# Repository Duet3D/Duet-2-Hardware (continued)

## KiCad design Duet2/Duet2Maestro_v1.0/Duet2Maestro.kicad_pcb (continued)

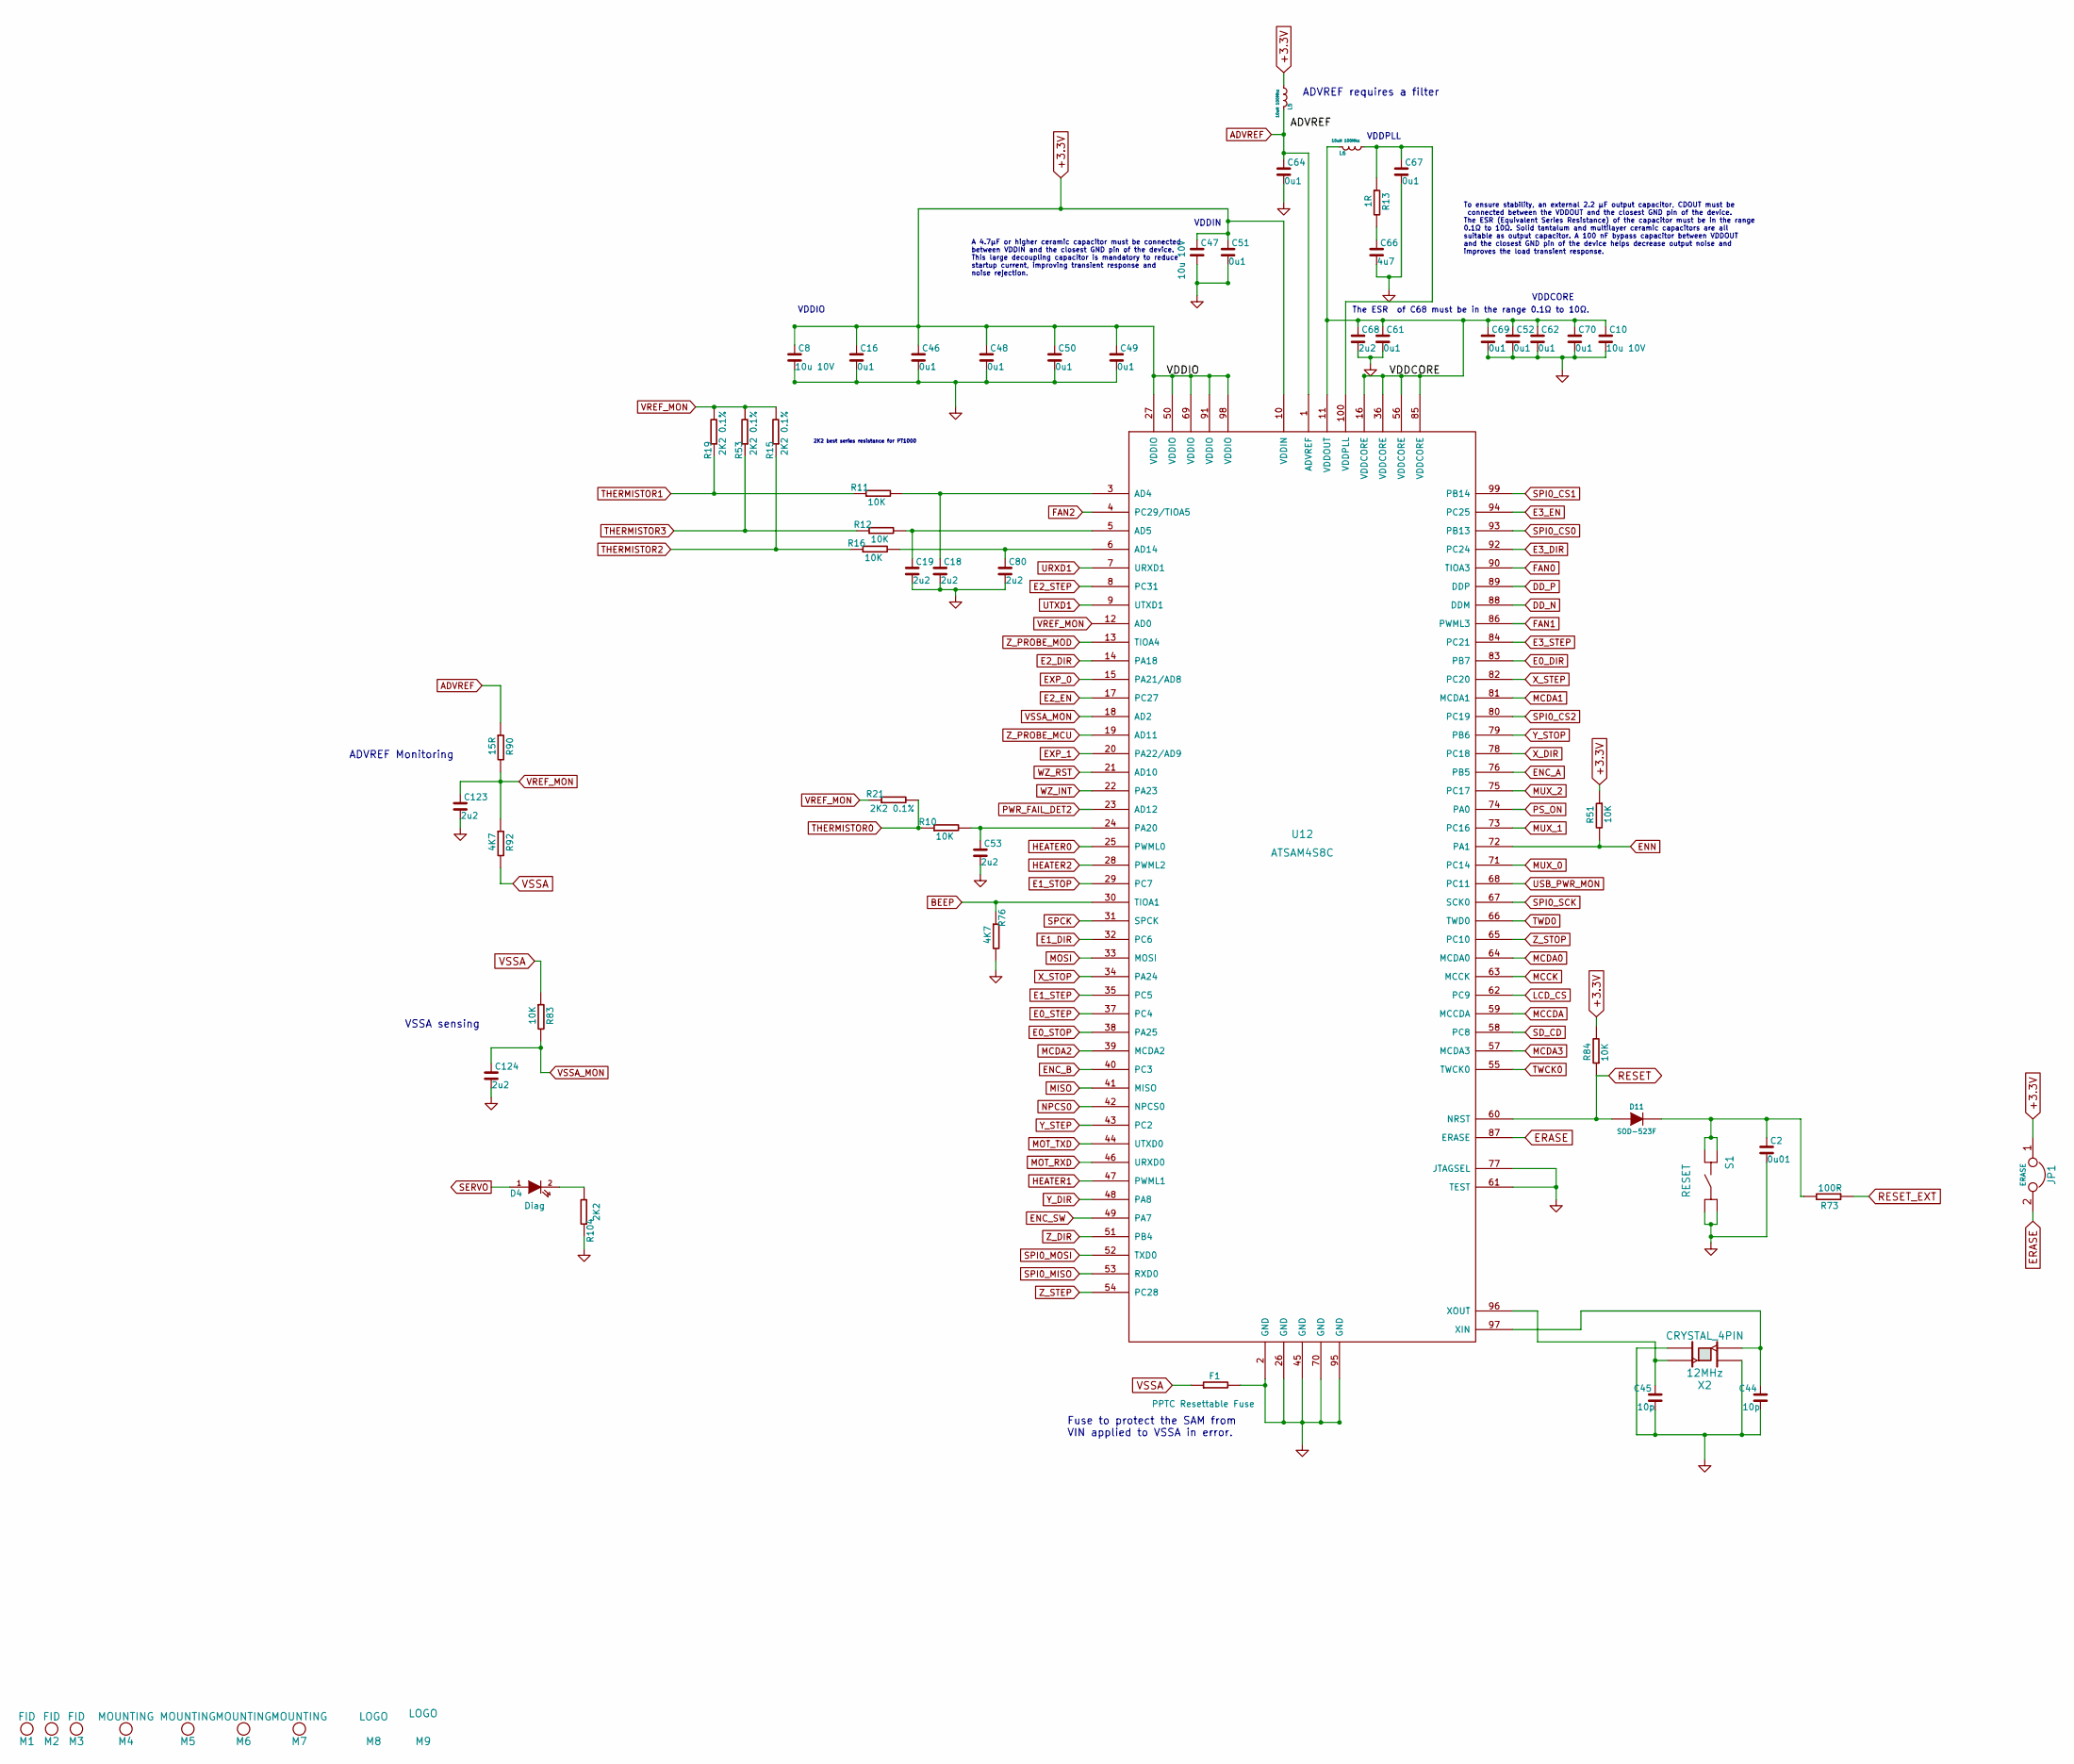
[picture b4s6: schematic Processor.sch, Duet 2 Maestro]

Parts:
C2: 0u01; C_0603
C8, C10, C47: 10u 10V; C_0805
C16, C46, C48, C49, C50, C51, C52, C61, C62, C64, C67, C69, C70: 0u1; C_0603
C18, C19, C53, C68, C80, C123, C124: 2u2; C_0603
C44, C45: 10p; C_0603
C66: 4u7; C_0805
D4: Diag; D_0603
D11: SOD-523F
F1: PPTC Resettable Fuse; R_1206
JP1: ERASE; JUMPER
L5, L6: 10uH 100Mhz; R_0603
M1, M2, M3: FID; Fiducial_1mm_Dia_2.54mm_Outer_CopperTop
M4, M5, M6, M7: MOUNTING; Fixing_M4
M8: LOGO; LOGO1
M9: LOGO; Plain_Wifi_Logo_m
R10, R11, R12, R16, R51, R83, R84: 10K; R_0603
R13: 1R; R_0603
R15, R19, R21, R53: 2K2 0.1%; R_0603
R73: 100R; R_0603
R76, R92: 4K7; R_0603
R90: 15R; R_0603
R104: 2K2; R_0603
S1: RESET; SW_SIDE_1_lugs
U12: ATSAM4S8C; LQFP-100_14x14mm_Pitch0.5mm
X2: CRYSTAL_4PIN; Xtal_5x3.2

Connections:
+3.3V: C8.1, C16.1, C46.1, C47.1, C48.1, C49.1, C50.1, C51.1, JP1.1, L5.2 (B), R51.1, R84.2, U12.10 (VDDIN), U12.27 (VDDIO), U12.50 (VDDIO), U12.69 (VDDIO), U12.91 (VDDIO), U12.98 (VDDIO); also elsewhere on the board
/Processor/VDDCORE: C10.1, C52.1, C61.1, C62.1, C68.1, C69.1, C70.1, L6.1 (A), U12.11 (VDDOUT), U12.16 (VDDCORE), U12.36 (VDDCORE), U12.56 (VDDCORE), U12.85 (VDDCORE)
ADVREF: C64.1, L5.1 (A), R90.1, U12.1 (ADVREF); also elsewhere on the board
BEEP: R76.1, U12.30 (TIOA1); also elsewhere on the board
DD_N: U12.88 (DDM); also elsewhere on the board
DD_P: U12.89 (DDP); also elsewhere on the board
E0_DIR: U12.83 (PB7); also elsewhere on the board
E0_STEP: U12.37 (PC4); also elsewhere on the board
E0_STOP: U12.38 (PA25); also elsewhere on the board
E1_DIR: U12.32 (PC6); also elsewhere on the board
E1_STEP: U12.35 (PC5); also elsewhere on the board
E1_STOP: U12.29 (PC7); also elsewhere on the board
E2_DIR: U12.14 (PA18); also elsewhere on the board
E2_EN: U12.17 (PC27); also elsewhere on the board
E2_STEP: U12.8 (PC31); also elsewhere on the board
E3_DIR: U12.92 (PC24); also elsewhere on the board
E3_EN: U12.94 (PC25); also elsewhere on the board
E3_STEP: U12.84 (PC21); also elsewhere on the board
ENC_A: U12.76 (PB5); also elsewhere on the board
ENC_B: U12.40 (PC3); also elsewhere on the board
ENC_SW: U12.49 (PA7); also elsewhere on the board
ENN: R51.2, U12.72 (PA1); also elsewhere on the board
ERASE: JP1.2, U12.87 (ERASE)
EXP_0: U12.15 (PA21/AD8); also elsewhere on the board
EXP_1: U12.20 (PA22/AD9); also elsewhere on the board
FAN0: U12.90 (TIOA3); also elsewhere on the board
FAN1: U12.86 (PWML3); also elsewhere on the board
FAN2: U12.4 (PC29/TIOA5); also elsewhere on the board
GND: C2.2, C8.2, C10.2, C16.2, C18.2, C19.2, C44.2, C45.2, C46.2, C47.2, C48.2, C49.2, C50.2, C51.2, C52.2, C53.2, C61.2, C62.2, C64.2, C66.2, C67.2, C68.2, C69.2, C70.2, C80.2, C123.2, C124.2, F1.2, R76.2, R104.1, S1.1, S1.2, U12.2 (GND), U12.26 (GND), U12.45 (GND), U12.61 (TEST), U12.70 (GND), U12.77 (JTAGSEL), U12.95 (GND), X2.2, X2.4; also elsewhere on the board
HEATER0: U12.25 (PWML0); also elsewhere on the board
HEATER1: U12.47 (PWML1); also elsewhere on the board
HEATER2: U12.28 (PWML2); also elsewhere on the board
LCD_CS: U12.62 (PC9); also elsewhere on the board
MCCDA: U12.59 (MCCDA); also elsewhere on the board
MCCK: U12.63 (MCCK); also elsewhere on the board
MCDA0: U12.64 (MCDA0); also elsewhere on the board
MCDA1: U12.81 (MCDA1); also elsewhere on the board
MCDA2: U12.39 (MCDA2); also elsewhere on the board
MCDA3: U12.57 (MCDA3); also elsewhere on the board
MISO: U12.41 (MISO); also elsewhere on the board
MOSI: U12.33 (MOSI); also elsewhere on the board
MOT_RXD: U12.46 (URXD0); also elsewhere on the board
MOT_TXD: U12.44 (UTXD0); also elsewhere on the board
MUX_0: U12.71 (PC14); also elsewhere on the board
MUX_1: U12.73 (PC16); also elsewhere on the board
MUX_2: U12.75 (PC17); also elsewhere on the board
NPCS0: U12.42 (NPCS0); also elsewhere on the board
unnamed: C2.1, D11.1 (K), R73.2, S1.3, S1.4
unnamed: C18.1, R11.2, U12.3 (AD4)
unnamed: C19.1, R12.2, U12.5 (AD5)
unnamed: C44.1, U12.97 (XIN), X2.3
unnamed: C45.1, U12.96 (XOUT), X2.1
unnamed: C53.1, R10.2, U12.24 (PA20)
unnamed: C66.1, R13.2
unnamed: C67.1, L6.2 (B), R13.1, U12.100 (VDDPLL)
unnamed: C80.1, R16.2, U12.6 (AD14)
unnamed: D4.2 (K), R104.2
PS_ON: U12.74 (PA0); also elsewhere on the board
PWR_FAIL_DET2: U12.23 (AD12); also elsewhere on the board
RESET: D11.2 (A), R84.1, U12.60 (NRST); also elsewhere on the board
RESET_EXT: R73.1; also elsewhere on the board
SD_CD: U12.58 (PC8); also elsewhere on the board
SERVO: D4.1 (A); also elsewhere on the board
SPCK: U12.31 (SPCK); also elsewhere on the board
SPI0_CS0: U12.93 (PB13); also elsewhere on the board
SPI0_CS1: U12.99 (PB14); also elsewhere on the board
SPI0_CS2: U12.80 (PC19); also elsewhere on the board
SPI0_MISO: U12.53 (RXD0); also elsewhere on the board
SPI0_MOSI: U12.52 (TXD0); also elsewhere on the board
SPI0_SCK: U12.67 (SCK0); also elsewhere on the board
THERMISTOR0: R10.1, R21.2; also elsewhere on the board
THERMISTOR1: R11.1, R19.1; also elsewhere on the board
THERMISTOR2: R15.1, R16.1; also elsewhere on the board
THERMISTOR3: R12.1, R53.1; also elsewhere on the board
TWCK0: U12.55 (TWCK0); also elsewhere on the board
TWD0: U12.66 (TWD0); also elsewhere on the board
URXD1: U12.7 (URXD1); also elsewhere on the board
USB_PWR_MON: U12.68 (PC11); also elsewhere on the board
UTXD1: U12.9 (UTXD1); also elsewhere on the board
VREF_MON: C123.1, R15.2, R19.2, R21.1, R53.2, R90.2, R92.1, U12.12 (AD0)
VSSA: F1.1, R83.1, R92.2; also elsewhere on the board
VSSA_MON: C124.1, R83.2, U12.18 (AD2)
WZ_INT: U12.22 (PA23); also elsewhere on the board
WZ_RST: U12.21 (AD10); also elsewhere on the board
X_DIR: U12.78 (PC18); also elsewhere on the board
X_STEP: U12.82 (PC20); also elsewhere on the board
X_STOP: U12.34 (PA24); also elsewhere on the board
Y_DIR: U12.48 (PA8); also elsewhere on the board
Y_STEP: U12.43 (PC2); also elsewhere on the board
Y_STOP: U12.79 (PB6); also elsewhere on the board
Z_DIR: U12.51 (PB4); also elsewhere on the board
Z_PROBE_MCU: U12.19 (AD11); also elsewhere on the board
Z_PROBE_MOD: U12.13 (TIOA4); also elsewhere on the board
Z_STEP: U12.54 (PC28); also elsewhere on the board
Z_STOP: U12.65 (PC10); also elsewhere on the board

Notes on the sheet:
VDDPLL
VDDCORE
VDDIO
VDDIN
To ensure stability, an external 2.2 μF output capacitor, CDOUT must be connected between the VDDOUT and the closest GND pin of the device. The ESR (Equivalent Series Resistance) of the capacitor must be in the range 0.1Ω to 10Ω. Solid tantalum and multilayer ceramic capacitors are all suitable as 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
Fuse to protect the SAM from VIN applied to VSSA in error.
The ESR of C68 must be in the range 0.1Ω to 10Ω.
ADVREF requires a filter
VSSA sensing
A 4.7µF or higher ceramic capacitor must be connected between VDDIN and the closest GND pin of the device. This large decoupling capacitor is mandatory to reduce startup current, improving transient response and noise rejection.
2K2 best series resistance for PT1000
ADVREF Monitoring

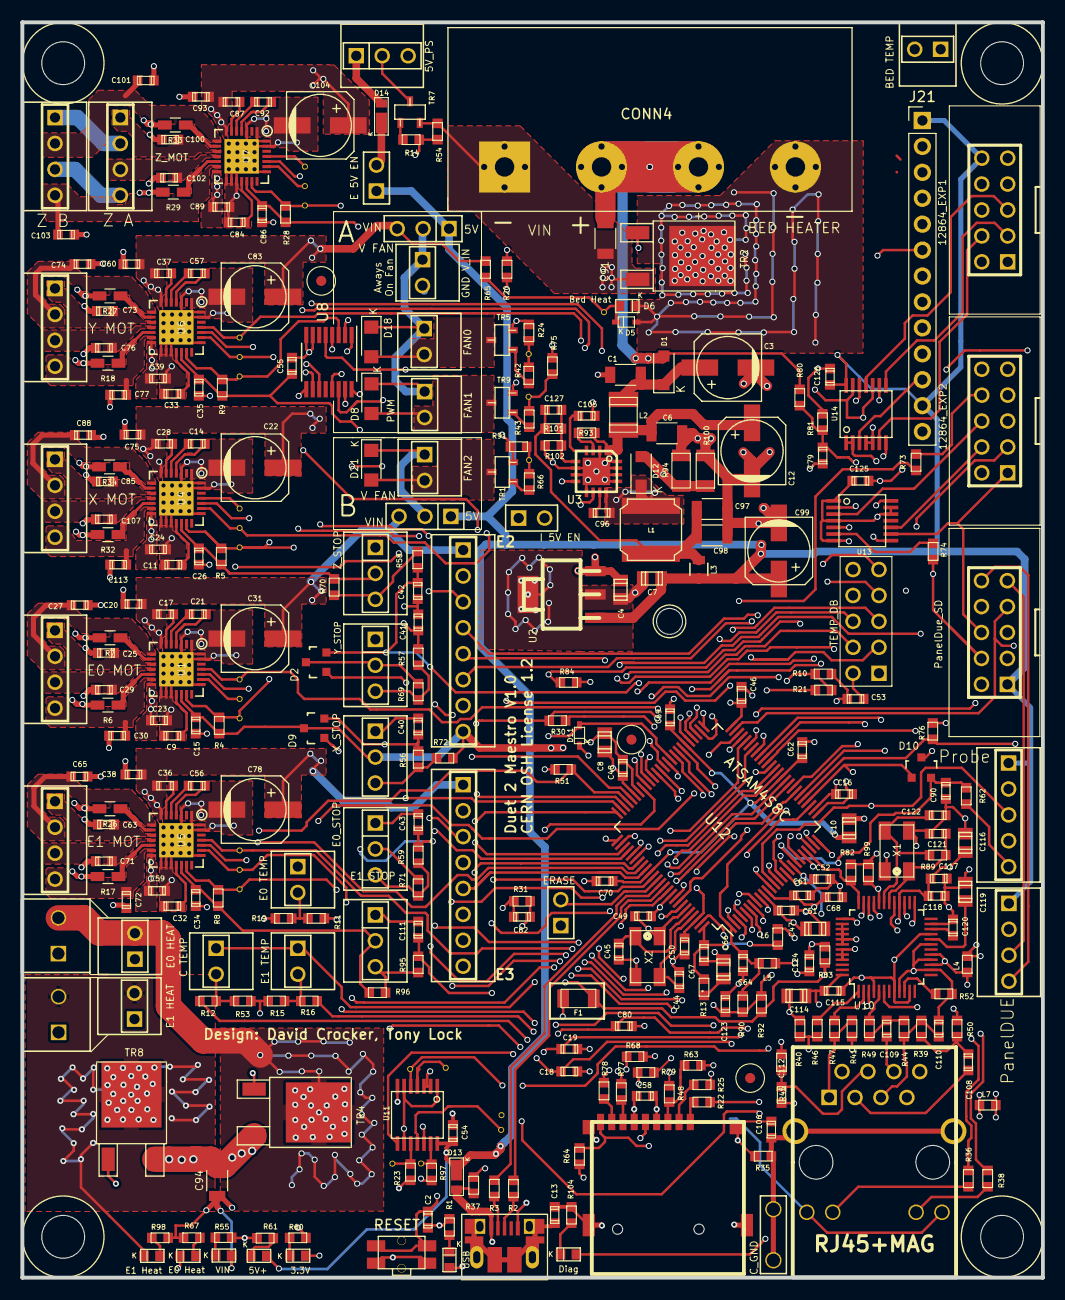
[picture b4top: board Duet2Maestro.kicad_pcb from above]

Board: 4 copper layers, 100.0 x 123.0 mm, 341 parts (1 on the bottom side), 243 nets.

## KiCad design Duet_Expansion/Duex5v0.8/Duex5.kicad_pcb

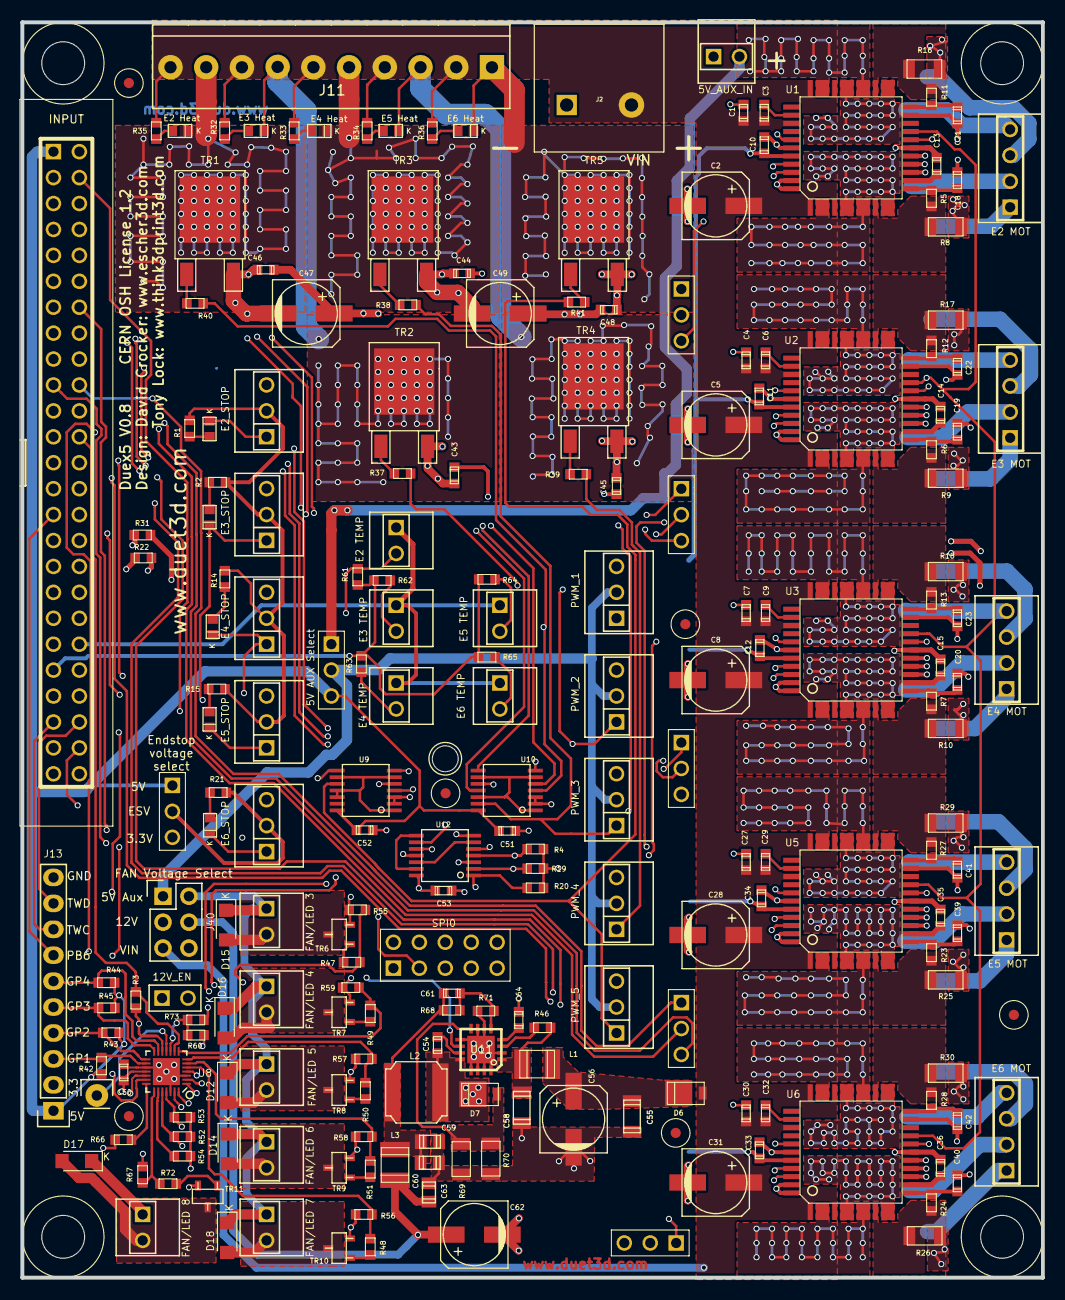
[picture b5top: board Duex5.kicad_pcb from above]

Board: 4 copper layers, 100.0 x 123.0 mm, 224 parts (1 on the bottom side), 179 nets.

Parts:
C1, C4, C7, C27, C30: 1u 50V; C_0603
C2, C5, C8, C28, C31, C56, C62: 100u 35V; C_ELEC_6.3x7.7
C3, C6, C9, C29, C32: 0u1 50V; C_0603
C10, C11, C12, C33, C34, C43, C44, C45, C46, C48, C50, C51, C52, C53, C64: 0u1; C_0603
C13, C14, C15, C35, C36: 0u47; C_0603
C18, C19, C20, C21, C22, C23, C39, C40, C41, C42: 0u01 X7R 10% 50V; C_0603
C47, C49: 100u; C_ELEC_6.3x7.7
C54: 22nF; C_0603
C55, C58: 10u 35V; C_1206
C59, C60, C63: 10u 16V; C_0805
C61: 0u01 16V; C_0603
D1: E2stp; D_0603
D2: E3stp; D_0603
D3: E4stp; D_0603
D4: E5stp; D_0603
D5: E6stp; D_0603
D6, D7: SS3P4; DO-220AA
D8: E3 Heat; D_0603
D9: E4 Heat; D_0603
D10: E5 Heat; D_0603
D11: E2 Heat; D_0603
D12, D14, D15, D16, D17, D18: DO-219AB
D13: E6 Heat; D_0603
J1: E2tp; CONN_3x1
J2: VIN; TERM_2-WAY_6.35mm
J3: E2 MOT; PIN_ARRAY_4x1
J4: E3tp; CONN_3x1
J5: E3 MOT; PIN_ARRAY_4x1
J6: 5V_AUX_IN; PIN_ARRAY_2X1
J7: E4tp; CONN_3x1
J8: E5tp; CONN_3x1
J9: E4 MOT; PIN_ARRAY_4x1
J10: E6tp; CONN_3x1
J11: CONN_01X10; TerminalBlock_Pheonix_PT-3.5mm_10pol
J12: E5 MOT; PIN_ARRAY_4x1
J13: CONN_01X10; Pin_Header_Straight_1x10
J14: E6 MOT; PIN_ARRAY_4x1
J15: FAN/LED 8; PIN_ARRAY_2X1
J16: INPUT; PIN_ARRAY_25X2
J19: E2 TEMP; PIN_ARRAY_2X1
J20: FAN/LED 3; PIN_ARRAY_2X1
J21: E3 TEMP; PIN_ARRAY_2X1
J22: PWM_1; PIN_ARRAY_3X1
J23: FAN/LED 4; PIN_ARRAY_2X1
J24: E4 TEMP; PIN_ARRAY_2X1
J25: FAN/LED 5; PIN_ARRAY_2X1
J26: PWM_2; PIN_ARRAY_3X1
J27: E5 TEMP; PIN_ARRAY_2X1
J28: FAN/LED 6; PIN_ARRAY_2X1
J29: E6 TEMP; PIN_ARRAY_2X1
J30: PWM_3; PIN_ARRAY_3X1
J31: FAN/LED 7; PIN_ARRAY_2X1
J32: PWM_4; PIN_ARRAY_3X1
J33: SPI0; MAX_TEMP_DB
J34: PWM_5; PIN_ARRAY_3X1
J35: E2_STOP; PIN_ARRAY_3X1
J36: E3_STOP; PIN_ARRAY_3X1
J37: E4_STOP; PIN_ARRAY_3X1
J38: E5_STOP; PIN_ARRAY_3X1
J39: E6_STOP; PIN_ARRAY_3X1
J40: CONN_02X03; Pin_Header_Straight_2x03
JP1: 5V AUX Select; CONN_3x1
JP2: 12V_EN; JUMPER
JP3: Endstop Voltage Select; CONN_3x1
L1, L3: 1uH; C_1210
L2: 10uH; L_6x6
M1, M2, M3, M9, M10, M11: FID; Fiducial_1mm_Dia_2.54mm_Outer_CopperTop
M4, M5, M6, M7: MOUNTING; Fixing_M4
M8: LOGO; LOGODX5
R1, R2, R3, R14, R15, R21, R47, R48, R49, R50, R51, R66, R72: 1K; R_0603
R4, R19, R20, R73: 0R; R_0603
R5, R6, R7, R11, R12, R13, R23, R24, R27, R28, R31: 22R; R_0603
R8, R9, R10, R16, R17, R18, R25, R26, R29, R30: 0R051; R_1206
R22: 3K3; R_0603
R32, R33, R34, R35, R36, R52, R53: 4K7; R_0603
R37, R38, R39, R40, R41: 180R; R_0603
R42, R43, R44, R45, R54, R55, R56, R57, R58, R59, R67: 10K; R_0603
R46: 200K; R_0603
R60: 0R DNP; R_0603
R61, R62, R63, R64, R65: 4K7 1%; R_0603
R68: 10.5K 1%; R_0603
R69, R70: 0R1; R_1206
R71: 750R 1%; R_0603
TP3: CONN_01X01; Pin_Header_Straight_1x01
TR1, TR2, TR3, TR4, TR5: IPD036N04L; D-PAK
TR6, TR7, TR8, TR9, TR10, TR11: PMV40UN2; SOT-23
U1, U2, U3, U5, U6: TMC2660
U8: SX1509B; QFN_4x4_28
U9, U10: 74HCT02; TSSOP-14
U11: A4403; QFN16-4x4
U12: 74HC32; TSSOP-14

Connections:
5V_S_F: J22.2, J26.2, J30.2, J32.2, J34.2, J40.1, JP1.2
12V: C62.1, C63.1, J40.4, L3.2
+3.3V: C10.1, C11.1, C12.1, C33.1, C34.1, C50.1, C53.1, J13.2, J16.3, J16.43, J33.8, JP3.3, R3.1, R22.2, R52.1, R53.1, R54.1, R60.1, U1.40, U2.40, U3.40, U5.40, U6.40, U8.4, U8.12, U8.18, U9.2, U9.3, U10.2, U10.3, U12.14
+5V: C51.1, C52.1, J13.1, J16.1, JP1.3, JP3.1, R42.1, R43.1, R44.1, R45.1, U9.14, U10.14
ADVREF: J16.41, R61.1, R62.1, R63.1, R64.1, R65.1
CS5: J16.50, J33.3
CS6: J16.9, J33.1
CS7: J16.14, J33.7
CS8: J16.19, J33.9
E2-: D11.2, J11.9, TR1.D
E2_DIR: J1.2, J16.6, U1.41
E2_EN: J1.3, J16.7, U1.18
E2_MOT_1A: J3.2, U1.5.6, U1.10.1
E2_MOT_1B: J3.1, U1.2.3, U1.7.8
E2_MOT_2A: J3.3, U1.26.7, U1.31.2
E2_MOT_2B: J3.4, U1.23.4, U1.28.9
E2_PWM: J22.1, R40.2, U10.4
E2_STEP: J1.1, J16.5, U1.42
E2_STOP: D1.2, J35.1, U8.27
E3-: D8.2, J11.7, TR2.D
E3_DIR: J4.2, J16.11, U2.41
E3_EN: J4.3, J16.12, U2.18
E3_MOT_1A: J5.2, U2.5.6, U2.10.1
E3_MOT_1B: J5.1, U2.2.3, U2.7.8
E3_MOT_2A: J5.3, U2.26.7, U2.31.2
E3_MOT_2B: J5.4, U2.23.4, U2.28.9
E3_PWM: J26.1, R37.2, U10.10
E3_STEP: J4.1, J16.10, U2.42
E3_STOP: D2.2, J36.1, U8.2
E4-: D9.2, J11.5, TR3.D
E4_DIR: J7.2, J16.16, U3.41
E4_EN: J7.3, J16.17, U3.18
E4_MOT_1A: J9.2, U3.5.6, U3.10.1
E4_MOT_1B: J9.1, U3.2.3, U3.7.8
E4_MOT_2A: J9.3, U3.26.7, U3.31.2
E4_MOT_2B: J9.4, U3.23.4, U3.28.9
E4_PWM: J30.1, R38.2, U10.13
E4_STEP: J7.1, J16.15, U3.42
E4_STOP: D3.2, J37.1, U8.1
E5-: D10.2, J11.3, TR4.D
E5_DIR: J8.2, J16.21, U5.41
E5_EN: J8.3, J16.22, U5.18
E5_MOT_1A: J12.2, U5.5.6, U5.10.1
E5_MOT_1B: J12.1, U5.2.3, U5.7.8
E5_MOT_2A: J12.3, U5.26.7, U5.31.2
E5_MOT_2B: J12.4, U5.23.4, U5.28.9
E5_PWM: J32.1, R39.2, U9.4
E5_STEP: J8.1, J16.20, U5.42
E5_STOP: D4.2, J38.1, U8.28
E6-: D13.2, J11.1, TR5.D
E6_DIR: J10.2, J16.26, U6.41
E6_EN: J10.3, J16.27, U6.18
E6_MOT_1A: J14.2, U6.5.6, U6.10.1
E6_MOT_1B: J14.1, U6.2.3, U6.7.8
E6_MOT_2A: J14.3, U6.26.7, U6.31.2
E6_MOT_2B: J14.4, U6.23.4, U6.28.9
E6_PWM: J34.1, R41.2, U9.10
E6_STEP: J10.1, J16.25, U6.42
E6_STOP: D5.2, J39.1, U8.20
ENN: J16.28, U1.19, U2.19, U3.19, U5.19, U6.19
ES_V: J35.2, J36.2, J37.2, J38.2, J39.2, JP3.2, R1.2, R2.2, R14.2, R15.2, R21.2
FAN3: R47.2, R55.2, U8.19
FAN3-: D15.2, J20.2, TR6.D
FAN4: R49.2, R59.1, U8.8
FAN4-: D16.2, J23.2, TR7.D
FAN5: R50.2, R57.2, U8.7
FAN5-: D12.2, J25.2, TR8.D
FAN6: R51.2, R58.2, U8.6
FAN6-: D14.2, J28.2, TR9.D
FAN7: R48.2, R56.2, U8.5
FAN7-: D18.2, J31.2, TR10.D
FAN8: R67.2, R72.2, U8.22
FAN8-: D17.2, J15.2, TR11.D
GND: C1.2, C2.2, C4.2, C5.2, C7.2, C8.2, C10.2, C11.2, C12.2, C13.2, C14.2, C15.2, C18.2, C19.2, C20.2, C21.2, C22.2, C23.2, C27.2, C28.2, C30.2, C31.2, C33.2, C34.2, C35.2, C36.2, C39.2, C40.2, C41.2, C42.2, C43.2, C44.2, C45.2, C46.2, C47.2, C48.2, C49.2, C50.2, C51.2, C52.2, C53.2, C55.2, C56.2, C58.2, C59.2, C60.2, C62.2, C63.2, C64.2, J2.1, J6.1, J13.10, J16.2, J16.30, J16.42, J22.3, J26.3, J30.3, J32.3, J33.2, J34.3, J35.3, J36.3, J37.3, J38.3, J39.3, JP2.1, R4.1, R8.1, R9.1, R10.1, R16.1, R17.1, R18.1, R19.1, R20.1, R25.1, R26.1, R29.1, R30.1, R55.1, R56.1, R57.1, R58.1, R59.2, R66.2, R67.1, R69.1, R70.1, R71.1, R73.2, TR1.S, TR2.S, TR3.S, TR4.S, TR5.S, TR6.S, TR7.S, TR8.S, TR9.S, TR10.S, TR11.S, U1.17, U1.21, U1.39, U1.43, U1.44, U2.17, U2.21, U2.39, U2.43, U2.44, U3.17, U3.21, U3.39, U3.43, U3.44, U5.17, U5.21, U5.39, U5.43, U5.44, U6.17, U6.21, U6.39, U6.43, U6.44, U8.3, U8.17, U8.26, U8.PAD, U9.7, U10.7, U11.2, U11.6, U11.7, U11.9, U11.13, U11.14, U11.15, U11.16, U11.17, U12.7
GPIO1: J13.3, R42.2, U8.16
GPIO2: J13.4, R43.2, U8.15
GPIO3: J13.5, R45.2, U8.14
GPIO4: J13.6, R44.2, U8.13
HEATER3: J16.8, U10.5
HEATER4: J16.13, U10.8
HEATER5: J16.18, U10.11
HEATER6: J16.23, U9.5
HEATER7: J16.31, U9.8
unnamed: C3.2, U1.35
unnamed: C6.2, U2.35
unnamed: C9.2, U3.35
unnamed: C13.1, U1.13
unnamed: C14.1, U2.13
unnamed: C15.1, U3.13
unnamed: C18.1, R5.2, U1.12
unnamed: C19.1, R6.2, U2.12
unnamed: C20.1, R7.2, U3.12
unnamed: C21.1, R11.2, U1.22
unnamed: C22.1, R12.2, U2.22
unnamed: C23.1, R13.2, U3.22
unnamed: C29.2, U5.35
unnamed: C32.2, U6.35
unnamed: C35.1, U5.13
unnamed: C36.1, U6.13
unnamed: C39.1, R23.2, U5.12
unnamed: C40.1, R24.2, U6.12
unnamed: C41.1, R27.2, U5.22
unnamed: C42.1, R28.2, U6.22
unnamed: C54.1, D7.2, L2.1, U11.12
unnamed: C54.2, U11.11
unnamed: C55.1, C56.1, D6.2, L1.1
unnamed: C58.1, L1.2, R46.2, U11.1
unnamed: C59.1, C60.1, C61.1, L2.2, L3.1, R68.2
unnamed: C61.2, R68.1, R71.2, U11.5
unnamed: C64.1, U11.4
unnamed: D1.1, R1.1
unnamed: D2.1, R2.1
unnamed: D3.1, R14.1
unnamed: D4.1, R15.1
unnamed: D5.1, R21.1
unnamed: D7.1, R69.2, R70.2, U11.8
unnamed: D8.1, R32.1
unnamed: D9.1, R33.1
unnamed: D10.1, R34.1
unnamed: D11.1, R35.1
unnamed: D13.1, R36.1
unnamed: J6.2, JP1.1
unnamed: J16.32, R31.2
unnamed: JP2.2, U11.10
unnamed: R5.1, R8.2, U1.9
unnamed: R6.1, R9.2, U2.9
unnamed: R7.1, R10.2, U3.9
unnamed: R11.1, R16.2, U1.25
unnamed: R12.1, R17.2, U2.25
unnamed: R13.1, R18.2, U3.25
unnamed: R23.1, R25.2, U5.9
unnamed: R24.1, R26.2, U6.9
unnamed: R27.1, R29.2, U5.25
unnamed: R28.1, R30.2, U6.25
unnamed: R37.1, TR2.G
unnamed: R38.1, TR3.G
unnamed: R39.1, TR4.G
unnamed: R40.1, TR1.G
unnamed: R41.1, TR5.G
unnamed: R46.1, U11.3
unnamed: R47.1, TR6.G
unnamed: R48.1, TR10.G
unnamed: R49.1, TR7.G
unnamed: R50.1, TR8.G
unnamed: R51.1, TR9.G
unnamed: R54.2, U8.23
unnamed: R60.2, R73.1, U8.10
unnamed: R66.1, U8.21
unnamed: R72.1, TR11.G
unnamed: U9.1, U9.6, U9.9, U9.11, U9.12
unnamed: U10.1, U10.6, U10.9, U10.12
unnamed: U12.3, U12.10
unnamed: U12.6, U12.12
unnamed: U12.8, U12.13
OSCIO: TP3.1, U8.11
PB6/TMS: J13.7, J16.29
SG_TST: J16.4, U12.11
SG_TST_E2: U1.38, U12.9
SG_TST_E3: U2.38, U12.5
SG_TST_E4: R4.2, U3.38, U12.4
SG_TST_E5: R19.2, U5.38, U12.2
SG_TST_E6: R20.2, U6.38, U12.1
SPI0_MISO: J16.49, J33.6
SPI0_MOSI: J16.48, J33.5
SPI0_SCK: J16.47, J33.4
SPI1_MISO: J16.34, R22.1, U1.14, U2.14, U3.14, U5.14, U6.14
SPI1_MOSI_BUFF: J16.33, U1.15, U2.15, U3.15, U5.15, U6.15
SPI1_SCK_BUFF_EXP: R31.1, U1.16, U2.16, U3.16, U5.16, U6.16
SX1509_INT: J16.24, R3.2, U8.9
THERMISTOR3: J16.35, J19.2, R61.2
THERMISTOR4: J16.36, J21.2, R62.2
THERMISTOR5: J16.37, J24.2, R63.2
THERMISTOR6: J16.38, J27.2, R64.2
THERMISTOR7: J16.39, J29.2, R65.2
TWCK0: J13.9, J16.46, R53.2, U8.25
TWD0: J13.8, J16.45, R52.2, U8.24
VSSA: J16.40, J19.1, J21.1, J24.1, J27.1, J29.1
V_FAN: D12.1, D14.1, D15.1, D16.1, D17.1, D18.1, J15.1, J20.1, J23.1, J25.1, J28.1, J31.1, J40.2, J40.3, J40.6
V_IN: C1.1, C2.1, C3.1, C4.1, C5.1, C6.1, C7.1, C8.1, C9.1, C27.1, C28.1, C29.1, C30.1, C31.1, C32.1, C43.1, C44.1, C45.1, C46.1, C47.1, C48.1, C49.1, D6.1, J2.2, J11.2, J11.4, J11.6, J11.8, J11.10, J40.5, R32.2, R33.2, R34.2, R35.2, R36.2, U1.1, U1.4, U1.30, U1.33, U1.36, U2.1, U2.4, U2.30, U2.33, U2.36, U3.1, U3.4, U3.30, U3.33, U3.36, U5.1, U5.4, U5.30, U5.33, U5.36, U6.1, U6.4, U6.30, U6.33, U6.36

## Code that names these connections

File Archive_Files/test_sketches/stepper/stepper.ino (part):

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If the end stops are not connected by a NC switch or wire short then set the relavent endStopDisabled=true
to disable the checking for them

For the E0_En and Z_EN pins the "SamNonDuePin" libaray allows access to pins that are not defined in the Arduino
Due software but are provided by the SAM3X8E, this library is still in development.

Various pins are not defined, or defined differently on the Arduino Due so the SamNonDuePin library is used to access them as standard I/O
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#define E3_POT_R 0x80
#define E4_POT_R 0x80

#define X_STEP 14
#define X_DIR 15
#define X_EN 29
#define X_STOP 11

#define Y_STEP 25
#define Y_DIR 26
#define Y_EN 27
#define Y_STOP 28

#define Z_STEP 5
#define Z_DIR 4
#define Z_EN X1//Sam pin PC27 not defined for Due
#define Z_STOP 60

#define E0_STEP X2 //Sam pin configured for CAN on Due
#define E0_DIR X3 //Sam pin configured for CAN on Due
#define E0_EN  X0//Sam pin pin PA5 not defined for Due
#define E0_STOP 31

#ifdef EXPANSION
#define E1_STEP 41
#define E1_DIR 35
#define E1_EN  37
#define E1_STOP 24

#define E2_STEP 39
#define E2_DIR 53
#define E2_EN  X8
#define E2_STOP 46

#define E3_STEP X4
#define E3_DIR 51
#define E3_EN  50
#define E3_STOP 45

#define E4_STEP 49
#define E4_DIR 48
#define E4_EN  47
#define E4_STOP 44
#endif

//use to disable the axis endstop checking code so the motors step regardless
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 #endif
 
 //Setup the pins for the Stepper drivers
 pinMode(X_STEP, OUTPUT);
 pinMode(X_DIR, OUTPUT);
 pinMode(X_EN, OUTPUT);
 pinMode(X_STOP, INPUT);
 
 pinMode(Y_STEP, OUTPUT);
 pinMode(Y_DIR, OUTPUT);
 pinMode(Y_EN, OUTPUT);
 pinMode(Y_STOP, INPUT);
 
 pinMode(Z_STEP, OUTPUT);
 pinMode(Z_DIR, OUTPUT);
 pinModeNonDue(Z_EN, OUTPUT);
 pinMode(Z_STOP, INPUT);
 
 pinModeNonDue(E0_STEP, OUTPUT);
 pinModeNonDue(E0_DIR, OUTPUT);
 pinModeNonDue(E0_EN, OUTPUT);
 pinMode(E0_STOP, INPUT);
#ifdef EXPANSION
 pinMode(E1_STEP, OUTPUT);
 pinMode(E1_DIR, OUTPUT);
 pinMode(E1_EN, OUTPUT);
 pinMode(E1_STOP, INPUT);
 
 pinMode(E2_STEP, OUTPUT);
 pinMode(E2_DIR, OUTPUT);
 pinModeNonDue(E2_EN, OUTPUT);
 pinMode(E2_STOP, INPUT);
 
 pinModeNonDue(E3_STEP, OUTPUT);
 pinMode(E3_DIR, OUTPUT);
 pinMode(E3_EN, OUTPUT);
 pinMode(E3_STOP, INPUT);
 
 pinMode(E4_STEP, OUTPUT);
 pinMode(E4_DIR, OUTPUT);
 pinMode(E4_EN, OUTPUT);
 pinMode(E4_STOP, INPUT);
#endif

//disable the steppers to begin
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
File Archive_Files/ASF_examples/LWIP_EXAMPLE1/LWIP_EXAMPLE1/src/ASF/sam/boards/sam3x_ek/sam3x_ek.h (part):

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/* SPI                                                                      */
/* ------------------------------------------------------------------------ */
/*! SPI0 MISO pin definition. */
#define SPI0_MISO_GPIO        (PIO_PA25_IDX)
#define SPI0_MISO_FLAGS       (PIO_PERIPH_A | PIO_DEFAULT)
/*! SPI0 MOSI pin definition. */
#define SPI0_MOSI_GPIO        (PIO_PA26_IDX)
#define SPI0_MOSI_FLAGS       (PIO_PERIPH_A | PIO_DEFAULT)
/*! SPI0 SPCK pin definition. */
#define SPI0_SPCK_GPIO        (PIO_PA27_IDX)
#define SPI0_SPCK_FLAGS       (PIO_PERIPH_A | PIO_DEFAULT)

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#define SPI0_NPCS3_PB23_FLAGS      (PIO_PERIPH_B | PIO_DEFAULT)

/*! SPI1 MISO pin definition. */
#define SPI1_MISO_GPIO             (PIO_PE28_IDX)
#define SPI1_MISO_FLAGS            (PIO_PERIPH_A | PIO_DEFAULT)
/*! SPI1 MOSI pin definition. */
#define SPI1_MOSI_GPIO             (PIO_PE29_IDX)
#define SPI1_MOSI_FLAGS            (PIO_PERIPH_A | PIO_DEFAULT)
/*! SPI1 SPCK pin definition. */
#define SPI1_SPCK_GPIO             (PIO_PE30_IDX)
#define SPI1_SPCK_FLAGS            (PIO_PERIPH_A | PIO_DEFAULT)
/*! SPI1 chip select 0 pin definition. (Only one configuration is possible) */
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	PIOE, ID_PIOE, PIO_PERIPH_B, PIO_PULLUP }


/** HSMCI MCCDA pin definition. */
#define PIN_HSMCI_MCCDA_GPIO            (PIO_PA20_IDX)
#define PIN_HSMCI_MCCDA_FLAGS           (PIO_PERIPH_A | PIO_DEFAULT)
/** HSMCI MCCK pin definition. */
#define PIN_HSMCI_MCCK_GPIO             (PIO_PA19_IDX)
#define PIN_HSMCI_MCCK_FLAGS            (PIO_PERIPH_A | PIO_DEFAULT)
/** HSMCI MCDA0 pin definition. */
#define PIN_HSMCI_MCDA0_GPIO            (PIO_PA21_IDX)
#define PIN_HSMCI_MCDA0_FLAGS           (PIO_PERIPH_A | PIO_DEFAULT)
/** HSMCI MCDA1 pin definition. */
#define PIN_HSMCI_MCDA1_GPIO            (PIO_PA22_IDX)
#define PIN_HSMCI_MCDA1_FLAGS           (PIO_PERIPH_A | PIO_DEFAULT)
/** HSMCI MCDA2 pin definition. */
#define PIN_HSMCI_MCDA2_GPIO            (PIO_PA23_IDX)
#define PIN_HSMCI_MCDA2_FLAGS           (PIO_PERIPH_A | PIO_DEFAULT)
/** HSMCI MCDA3 pin definition. */
#define PIN_HSMCI_MCDA3_GPIO            (PIO_PA24_IDX)
#define PIN_HSMCI_MCDA3_FLAGS           (PIO_PERIPH_A | PIO_DEFAULT)
/** HSMCI MCDA4 pin definition. */
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/* ------------------------------------------------------------------------ */
/* UART                                                                     */
/* ------------------------------------------------------------------------ */
/*! UART pins (UTXD0 and URXD0) definitions, PA8,9. */
#define PINS_UART        (PIO_PA8A_URXD | PIO_PA9A_UTXD)
#define PINS_UART_FLAGS  (PIO_PERIPH_A | PIO_DEFAULT)

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
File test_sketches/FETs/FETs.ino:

/*
Test code for FET outputs on DUET v0.4/v0.5 and expansion board v0.1
Note on 0.3/0.4 the FETS come on automatically when 12V is applied (the driver fets invert
the logic)

On version 0.5 and expansion board v0.1 the fet logic is inverted.

Uses the Undefined Arduino Due Pins Library "SamNonDuePin" to demonstrate PWM on
pins that are not defined as PWM within the DUE software but are on the SAM3X8E

Note no setup of the pins is required as this is carried out within the analogWriteUndefined()
function in the same way as it is done within the normal analogWrite() function in arduino.

the following pins are connected:
E0_PWM    PIO_PC8B_PWML3   // Undefined pin 5
FAN0_PWM  PIO_PC2B_PWML0   // Undefined pin 6
BED_PWM   Arduino digital pin 6
E1_PWM  PIO_PC6B_PWML2   // Undefined pin 6
E2_PWM  Arduino digital pin 9
E3_PWM  Arduino digital pin 8
E4_PWM  Arduino digital pin 7

Finally I am using the option of defining the Arduino Undef pins with a X in front of them, 
this allows for them to be more easily distinguised from arduino pins.
*/

#define EXPANSION

#include "Arduino.h"
#include "SamNonDuePin.h"

#define E0_PWM X5  
#define FAN0_PWM X6 
#define BED_PWM 6
#ifdef EXPANSION
#define E1_PWM X7
#define E2_PWM 9
#define E3_PWM 8
#define E4_PWM 7
#endif

void setup() {
}

void loop() {
  for (int i = 0 ; i<256 ;i++)
  { 
    analogWriteNonDue(FAN0_PWM, i);
    analogWriteNonDue(E0_PWM, i);
    analogWrite(BED_PWM, i);
#ifdef EXPANSION
    analogWriteNonDue(E1_PWM, i);
    analogWrite(E2_PWM, i);
    analogWrite(E3_PWM, i);
    analogWrite(E4_PWM, i);
#endif    
    delay(10);
  }
  delay(500); 
  for (int i = 255 ; i>=0 ;i--)
  { 
    analogWriteNonDue(FAN0_PWM, i);
    analogWriteNonDue(E0_PWM, i);
    analogWrite(BED_PWM, i);
#ifdef EXPANSION
    analogWriteNonDue(E1_PWM, i);
    analogWrite(E2_PWM, i);
    analogWrite(E3_PWM, i);
    analogWrite(E4_PWM, i);
#endif    
    delay(10);
  }
  delay(500);  
}

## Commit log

2013-04-11 Test Sketches first commit.
2013-04-11 Added analog input test code
    The ADC calcs.txt shows the theoretical ADC values based on the nominal
    resistance from an EPCOS B57560G104F thermistor with a Vanalog of 3.3V,
    measured with an ADC resolution of 10bits.
2013-04-15 LwIP Example Added
    Adapted from the Atmel Studio Framework example for SAM3X-EK:
    http://www.atmel.com/tools/AVRSOFTWAREFRAMEWORK.aspx
    More info on LwIP can be found here
    http://lwip.wikia.com/wiki/LwIP_Wiki
2013-04-15 Ignore AS project files
2013-04-16 Undefined Due pins example
    The stepper sketch has been updated to move all 4 steppers and to work
    with the
    UdefDuePin library which is the beginnings of a library to access the
    SAM3X8E pins that are not defined by the Arduino software
2013-04-18 Added E1 example on expansion header pins
    To allow for testing and comparison of other stepper driver chips and
    boards three expansion header pins(PC14,PC15,PC16) are configured as
    E1_DIR, E1_STEP and E1_EN.
2013-04-18 Added E1_STOP for completeness
    See previous commit description for explanation of E1.
2013-04-25 PWM demonstration in FETs.ino
    Updated the UdefDuePin library to carry out analog write on SAM3X8E PWM
    pins that are not defined within the default arduino pin allocations.
2013-05-19 Renamed UdefDuePin library to SamNonDuePin
    Changed the name of the Library and the functions within it to be
    clearer why it is used.
    Updated the example sketches that used the old library to use the new.
2013-05-19 HSMCI SD Card libaray and test sketch
    First draft of a library to access SD cards over the HSMCI interface
2013-05-28 Removed printf statements and other minor changes
    Reduced the compile size of the library by commenting out printf
    statements.
2013-05-28 Added the Example projects for Eclipse and Due
    See Readme.md for more info
2013-07-18 Added the Ethernet Atmel Studio 6.1 example
    Modification of the original LWIP project from the ASF example for the
    SAM3X8H development board to run on the SAM3X8E with the KSZ8051RNL PHY.
2013-09-10 Update FET example for 0.4
    and changed SamNonDuePin.cpp to reflect new PWM pins
2013-09-15 Expansion board support added to test sketches
    The SamNonDuePin library has also been updated.
2013-12-02 Archived old files
2013-12-02 Duet 0.6 added
    For more info check out www.think3dprint3d.com/duet
2013-12-02 Expansion Board v0.2 Added
    For more info check out www.think3dprint3d.com/duet
2013-12-30 Added Duet0.3 archive files
    Info here:
    http://blog.think3dprint3d.com/2013/12/duet-fet-psu-and-steppertesting.html
2014-01-15 Duet 0.4 design files added to archive
2014-04-17 Update digipot test sketch
    To work with new MCP4461 library:
    https://github.com/jmgiacalone/Arduino-libraries/tree/master/MCP4461
2014-10-30 Started work on Duet Shield.
2014-10-31 More work on the Duet shield.
2014-10-31 More spec...
2014-10-31 Final(?) spec of the Duet shield.
2014-10-31 Ground plane requirement added.
2014-11-05 Preparing the shield design to be based on the Duet 0.7.
2014-11-05 Duet 0.7 now copied and renamed as Shield.
2014-11-06 All schematic connections to the stepper drivers, heaters, and thermistors complete.
2014-11-06 About 75% of the schematic changes made.
2014-11-06 First hack at the shield schematic.
2014-11-07 Inputs and outputs tidied to keep DRC a bit happier...
2014-11-07 Header labels corrected.
2014-11-07 Connector pads and pins matched up (I hope...)
2014-11-13 Started PCB layout for Shield.
2014-11-14 PCB outline added.
2014-11-14 Minor tidying...
2014-11-14 Some pin headers provisionally positioned.
2014-11-17 Split shield development into two stages:
    Stage 1: 2 heaters + 2 stepper drivers
    Stage 2: 2 extra stepper drivers, 5-motor stepper ribbon, expansion connector
    This is the cut down version ready for Stage 1.
2014-11-17 First hack at all the component positions on the Shield board. No routing done yet.
2014-11-17 Spade connector module added.
2014-11-18 Shield spade connectirs used for power.
2014-11-18 File tidying.
2014-11-18 Ground plane added.
2014-11-18 Intermediate save
2014-11-18 Footprints got corrupted somehow. Fixed here.
2014-11-18 Gnd pad of stepper drivers modified to include heat dissipation vias.
2014-11-18 About 30% of the Shield routing done.
2014-11-19 More Shield routing done...
2014-11-19 More routing done...
2014-11-21 First complete Shield design.
2014-11-22 Shield 0.2 design started - 4 stepper drivers + ribbon cable.
2014-11-24 Gerbers done.
2014-11-24 BoM added.
2014-12-12 Duet V0.6a
    Ground plane added, and mounting holes grounded.
2014-12-12 V0.7a
    Complete ground plane added.
2014-12-15 Corrected the address of the digital potentiometer on the Shield. It is now the same as the expansion board. Also removed the pullup resistors on Shield lines TWCK0 and TWD0 as there are pullups on t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
2014-12-15 Changed version numbers to reflect Duet numbers.
2014-12-15 Shorts added to solder links for microstepping - should now step 16th.
2014-12-15 Tidying...
2014-12-15 New version of Duet 0.7 - Duet 0.7a with ground plane, no chokes, and stepper and heater pin headers in the same places as on the Duet 0.6.
2014-12-15 File tidying...
2014-12-16 Shield fan header wrong-way-round mistake fixed.
2014-12-16 Shield: swapped the location of P1 with J2 and J4, to make it easier to connect the hotend fan looms; removed chokes
2014-12-17 Shield - big cap between power connections moved. Parallel conn for Fan0 added.
2014-12-17 Tell-tale LEDs added to shield.
2014-12-17 Tell-tale LEDs added to Duet 0.7a.
2015-01-14 Updating Duet 0.7a...
2015-01-14 Updated silk screen on shield to move borad name.
2015-01-14 Silks for both new Duet and Shield improved. Versions incremented to Duet 0.7b and Shield V0.3.
2015-01-16 Power connector changed to 7.5mm pitch and nearby components moved to accommodate that. 10u capacitor added across the power supply to the probe socket.
2015-02-27 Duet Version 0.8 ----------------
    Schematic changed; board still needs to be updated.
    Changes:
    Probe rewired to use AD12 and AD14, (standard P2 probe in the Firmware)
    Bed connector - both spades and screw terminals used
    Power connector - both spades and screw terminals used
    Spurious power LEDS removed - there is now only one set
2015-02-27 Board half done...
2015-02-27 Power connector moved to be in same position as FDuet 0.6.
2015-02-27 This is the first complete version. But it has not been checked for errors.
2015-03-02 Spurious tracks added to the Duet design where fill will render them redundant. This makes Kicad show unconnected nodes correctly.
2015-03-02 Gerbers added. Note that the gerber files for layer Inner 2 and back have been swapped so that the ground plane is on the back.
2015-03-02 This time with the right version number on the front silk...
2015-03-04 Details of new reset and erase switches added to the BoM CSV file.
2015-03-05 Set-up for the development of Shield Version 0.4. This will (if there's room...) have 4 stepper drivers.
2015-03-05 Intermediate save of new shield layout.
2015-03-06 Shield V0.4 - WIP
2015-03-09 Shield V0.4 WIP
2015-03-10 Shield 0.4 WIP
2015-03-10 Yet more WIP...
2015-03-18 Tony's suggestion of re-instating the external 5V supply implemented. Power LEDS more widely spaced to allow easier access by printed light-pipe.
2015-03-18 This time with the ground plane swapped to the outside. (Not sure if this is a good idea. Cf. discussion with Jean-Marc.)
2015-03-18 Shield WIP.
2015-03-19 Power indicator LEDS moved to allow them to be in the same position on the shield.
2015-03-19 Shield WIP
2015-03-22 Bringing BOMs up to date.
2015-03-24 More Shield WIP
2015-03-25 Shield V0.4. First complete design.
2015-03-26 Layer swap to get ground plane on the back removed (the system doesn't generate mask files for internal layers, so swapping an internal layer for an outer one won't work...)
2015-04-07 Duet 0.6 BoM CSV added.
2015-04-12 Changed folder structure
2015-04-12 Duex4 v0.2a KiCAD files
2015-04-16 Importing Changes from RRP Dev branch
2015-07-06 Changed test sketch to report on SerialUSB
2015-08-06 Rename Duet to Duet0.6
    Rename in prep for Duet0.8.5 upload
2015-08-07 Duet0.8.5 KiCAD source files
    The source files for the Duet 0.8.5 3d printer electronics design.
    Licensed under the CERN OHL v1.2
2016-04-11 Re-arranged directory structure
2016-04-11 Added Duex4 2a Schematic pdf
2016-08-28 Update LICENSE
2016-08-28 Update LICENSE and README
2016-08-28 DuetWifiv1.0 Initial Commit
    The DuetWifi hardware design files in KiCAD. For details on the Duet
    wifi see the README file
2016-09-04 Added pdf Schematic
2016-09-05 Added contents of SD card
2017-01-06 Schematic footprint error correction
    The schematic specified the SAM3X8E footprint as a LQFP100. this
    corrects this to LQFP144
2017-01-12 Added Duex2/5 Source
2017-01-30 Added V1.01 Sources
2017-04-20 Added DuetWifi v1.02 KiCAD files
    And updated directory structure
2017-04-20 KiCAD library for Duet
2017-04-20 Duet Ethernet Module
2017-07-12 Added Duex5_v0.8
2017-07-13 Added Expansion Breakout v1.0 source files
2017-10-08 SD Card Contents
    As at August 2017. Read the readme
2017-10-08 add gcodes folder
    empty folder not added intially
2017-10-22 SD Card Contents Zip file
2017-12-25 Directory refactoring
    Clarified the Duet 2 (Wifi or bare board + Ethernet Module) version structure.
2017-12-25 Duet2v1.03 source files published
    Minor updates see https://duet3d.com/wiki/Hardware_overview#Version_History for changes from previous versions.
2017-12-25 Moved SD card contents
2018-07-16 Duet2_v1.04
2018-08-23 SD card contents updated
2018-08-30 Duet 2 Maestro source files
2018-08-30 Updated License to inclide Maestro
2018-08-30 Revert "Updated License to inclide Maestro"
    This reverts commit 1e5b497416f46327eace1a99e4fb97e521c40ee0.
2018-08-30 Updated License to include Duet 2 Maestro
2018-10-27 Archived Obsolete Duet Designs
2018-10-27 Archived Obsolete Duex Files
2018-10-27 archived v1.03
2018-11-10 Rename to v1.1
    Expansion Breakout board version was incorrect at v1.0 (that was a in house development version) Verison 1.1 is the shipped version.
2018-11-11 Added Wiring Diagram svg
    Added the wiring diagram as an SVG.
2019-03-05 Update Duet2/Duet2v1.04/DuetWifiv1.04a_Schematic.pdf
    New schematic with JTAG header removed.
2019-05-03 Updated default SD card contents
2019-07-01 Duex5v0.9
    The PCB revision 0.9a update for Duex 2 and Duex 5 v0.9 and v0.9a
2019-07-21 Fixed errors in wiring diagram
2019-10-09 V1.04a schematic
2019-10-09 Duet 2 Wifi v1.04b schematic
2019-10-09 Duet 2 v1.04c schematic
2019-10-23 Expansion Breakout STEP upload
2020-02-07 Ethernet Module Kicad project added
2020-02-16 Added Duex 5/2, updated to Duet3D where appropriate
2020-04-15 Create Duet2Maestro_Wiring_V1.0_drawing_v1.2.svg
    new drawing version fixing thermistor labelling
2020-04-30 Updated wiring diagram
    Motor phase labelling now matches the silkscreen.
2020-10-05 svg wiring diagrams added
2020-12-16 added schematic and ibom for Duex5v0.10
2021-02-08 clarified motor connections
2022-01-22 Rename README to README.md
2022-02-17 Documentation Link Updates
2022-05-01 corrected directory name for Duex5 v0.10
2022-05-01 Added Duexv0.11 KiCAD files
2022-10-26 Duex5 v0.11 iBOM
    also rescue files as the schematic would not load.
2023-07-24 added v1.05 KiCAD source
2023-11-27 v1.06 KiCAD project Files
2024-06-10 IR sensor STEP
2026-06-17 Replaced x0rtrunks with droftarts
